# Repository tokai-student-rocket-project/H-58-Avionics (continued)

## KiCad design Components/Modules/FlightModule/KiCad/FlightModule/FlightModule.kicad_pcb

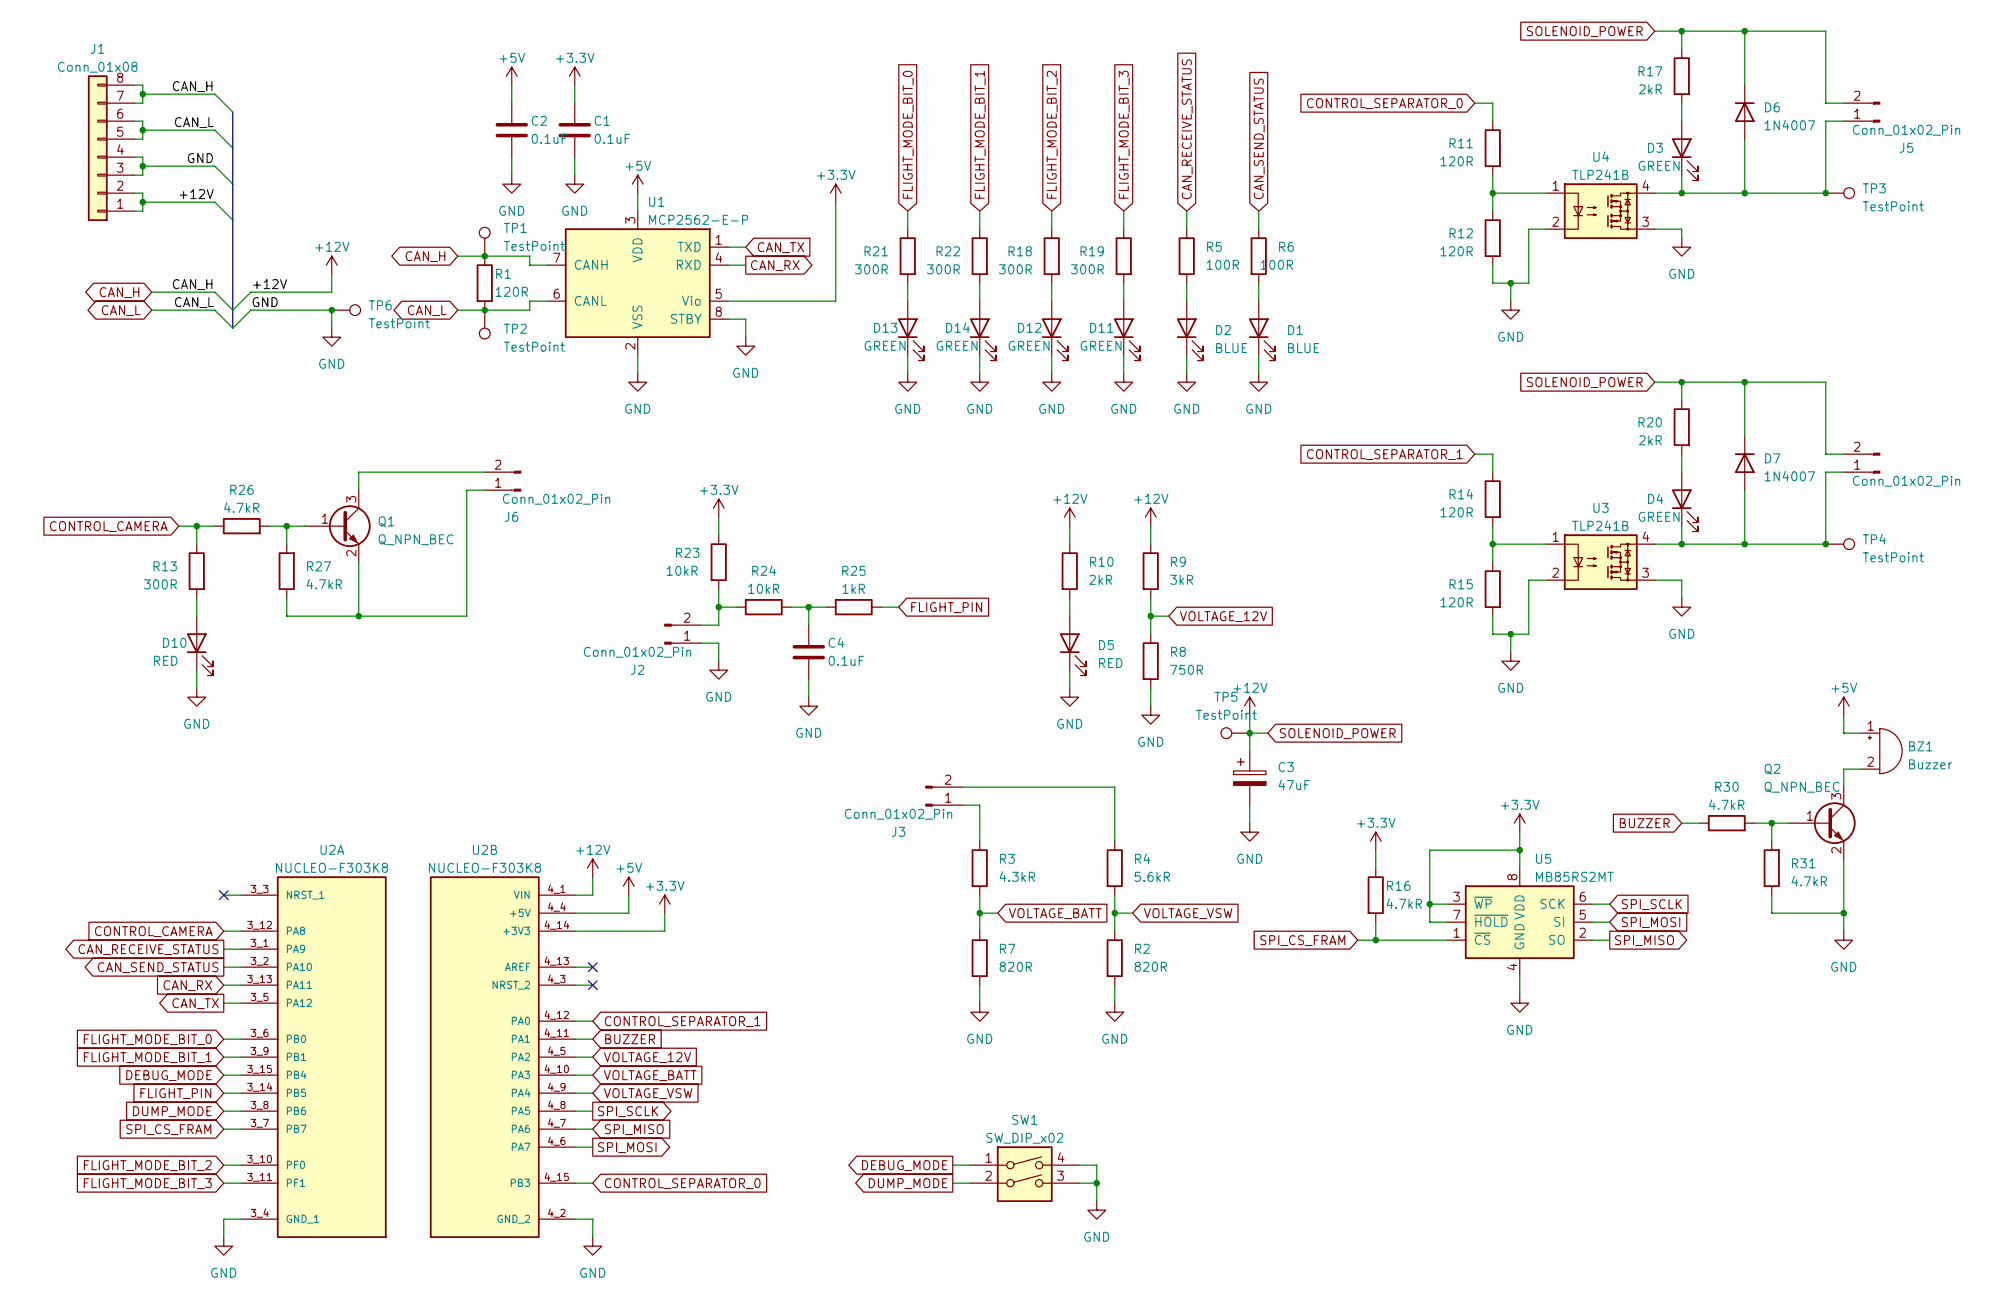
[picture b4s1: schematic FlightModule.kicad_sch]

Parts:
BZ1: Buzzer; Buzzer_12x9.5RM7.6
C1, C2, C4: 0.1uF; C_0603_1608Metric_Pad1.08x0.95mm_HandSolder
C3: 47uF; CP_Elec_6.3x5.9
D1, D2: BLUE; LED_0603_1608Metric_Pad1.05x0.95mm_HandSolder
D3, D4, D11, D12, D13, D14: GREEN; LED_0603_1608Metric_Pad1.05x0.95mm_HandSolder
D5, D10: RED; LED_0603_1608Metric_Pad1.05x0.95mm_HandSolder
D6, D7: 1N4007; D_SOD-123F
J1: Conn_01x08; Hirose_DF11B-8DP-2DS
J2, J3, J4, J5, J6: Conn_01x02_Pin; Hirose_DF1B
Q1, Q2: Q_NPN_BEC; SC-59_Handsoldering
R1, R11, R12, R14, R15: 120R; R_0603_1608Metric_Pad0.98x0.95mm_HandSolder
R2, R7: 820R; R_0603_1608Metric_Pad0.98x0.95mm_HandSolder
R3: 4.3kR; R_0603_1608Metric_Pad0.98x0.95mm_HandSolder
R4: 5.6kR; R_0603_1608Metric_Pad0.98x0.95mm_HandSolder
R5, R6: 100R; R_0805_2012Metric_Pad1.20x1.40mm_HandSolder
R8: 750R; R_0603_1608Metric_Pad0.98x0.95mm_HandSolder
R9: 3kR; R_0603_1608Metric_Pad0.98x0.95mm_HandSolder
R10, R17, R20: 2kR; R_0603_1608Metric_Pad0.98x0.95mm_HandSolder
R13, R18, R19, R21, R22: 300R; R_0603_1608Metric_Pad0.98x0.95mm_HandSolder
R16, R26, R27, R30, R31: 4.7kR; R_0603_1608Metric_Pad0.98x0.95mm_HandSolder
R23, R24: 10kR; R_0805_2012Metric_Pad1.20x1.40mm_HandSolder
R25: 1kR; R_0603_1608Metric_Pad0.98x0.95mm_HandSolder
SW1: SW_DIP_x02; SW_DIP_SPSTx02_Piano_10.8x6.64mm_W7.62mm_P2.54mm
TP1, TP2, TP3, TP4, TP5, TP6: TestPoint; Pin_D1.0mm_L10.0mm
U1: MCP2562-E-P; DIP-8_W7.62mm
U2: NUCLEO-F303K8; MODULE_NUCLEO-F303K8; PARTREV 5
U3, U4: TLP241B; DIP-4_W7.62mm
U5: MB85RS2MT; DIP-8_W7.62mm

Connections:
+3.3V: C1.1, R16.1, R23.1, U1.5 (Vio), U2.4_14 (+3V3), U5.3 (~WP), U5.7 (~HOLD), U5.8 (VDD)
+5V: BZ1.1 (-), C2.1, U1.3 (VDD), U2.4_4 (+5V)
BUZZER: R30.1, U2.4_11 (PA1)
CAN_H: J1.7, J1.8, R1.1, TP1.1, U1.7 (CANH)
CAN_L: J1.5, J1.6, R1.2, TP2.1, U1.6 (CANL)
CAN_RECEIVE_STATUS: R5.1, U2.3_1 (PA9)
CAN_RX: U1.4 (RXD), U2.3_13 (PA11)
CAN_SEND_STATUS: R6.1, U2.3_2 (PA10)
CAN_TX: U1.1 (TXD), U2.3_5 (PA12)
CONTROL_CAMERA: R13.1, R26.1, U2.3_12 (PA8)
CONTROL_SEPARATOR_0: R11.1, U2.4_15 (PB3)
CONTROL_SEPARATOR_1: R14.1, U2.4_12 (PA0)
DEBUG_MODE: SW1.1, U2.3_15 (PB4)
DUMP_MODE: SW1.2, U2.3_8 (PB6)
FLIGHT_MODE_BIT_0: R21.1, U2.3_6 (PB0)
FLIGHT_MODE_BIT_1: R22.1, U2.3_9 (PB1)
FLIGHT_MODE_BIT_2: R18.1, U2.3_10 (PF0)
FLIGHT_MODE_BIT_3: R19.1, U2.3_11 (PF1)
FLIGHT_PIN: R25.1, U2.3_14 (PB5)
GND: C1.2, C2.2, C3.2, C4.2, D1.1 (K), D2.1 (K), D5.1 (K), D10.1 (K), D11.1 (K), D12.1 (K), D13.1 (K), D14.1 (K), J1.3, J1.4, J2.1, Q2.2 (E), R2.2, R7.2, R8.2, R12.2, R15.2, R31.1, SW1.3, SW1.4, TP6.1, U1.2 (VSS), U1.8 (STBY), U2.3_4 (GND_1), U2.4_2 (GND_2), U3.2, U3.3, U4.2, U4.3, U5.4 (GND)
unnamed: BZ1.2 (+), Q2.3 (C)
unnamed: C4.1, R24.1, R25.2
unnamed: D1.2 (A), R6.2
unnamed: D2.2 (A), R5.2
unnamed: D3.2 (A), R17.2
unnamed: D3.1 (K), D6.2 (A), J5.1, TP3.1, U4.4
unnamed: D4.2 (A), R20.2
unnamed: D4.1 (K), D7.2 (A), J4.1, TP4.1, U3.4
unnamed: D5.2 (A), R10.2
unnamed: D10.2 (A), R13.2
unnamed: D11.2 (A), R19.2
unnamed: D12.2 (A), R18.2
unnamed: D13.2 (A), R21.2
unnamed: D14.2 (A), R22.2
unnamed: J2.2, R23.2, R24.2
unnamed: J3.1, R3.1
unnamed: J3.2, R4.1
unnamed: J6.1, Q1.2 (E), R27.1
unnamed: J6.2, Q1.3 (C)
unnamed: Q1.1 (B), R26.2, R27.2
unnamed: Q2.1 (B), R30.2, R31.2
unnamed: R11.2, R12.1, U4.1
unnamed: R14.2, R15.1, U3.1
SOLENOID_POWER: C3.1, D6.1 (K), D7.1 (K), J1.1, J1.2, J4.2, J5.2, R9.1, R10.1, R17.1, R20.1, TP5.1, U2.4_1 (VIN)
SPI_CS_FRAM: R16.2, U2.3_7 (PB7), U5.1 (~CS)
SPI_MISO: U2.4_7 (PA6), U5.2 (SO)
SPI_MOSI: U2.4_6 (PA7), U5.5 (SI)
SPI_SCLK: U2.4_8 (PA5), U5.6 (SCK)
VOLTAGE_12V: R8.1, R9.2, U2.4_5 (PA2)
VOLTAGE_BATT: R3.2, R7.1, U2.4_10 (PA3)
VOLTAGE_VSW: R2.1, R4.2, U2.4_9 (PA4)

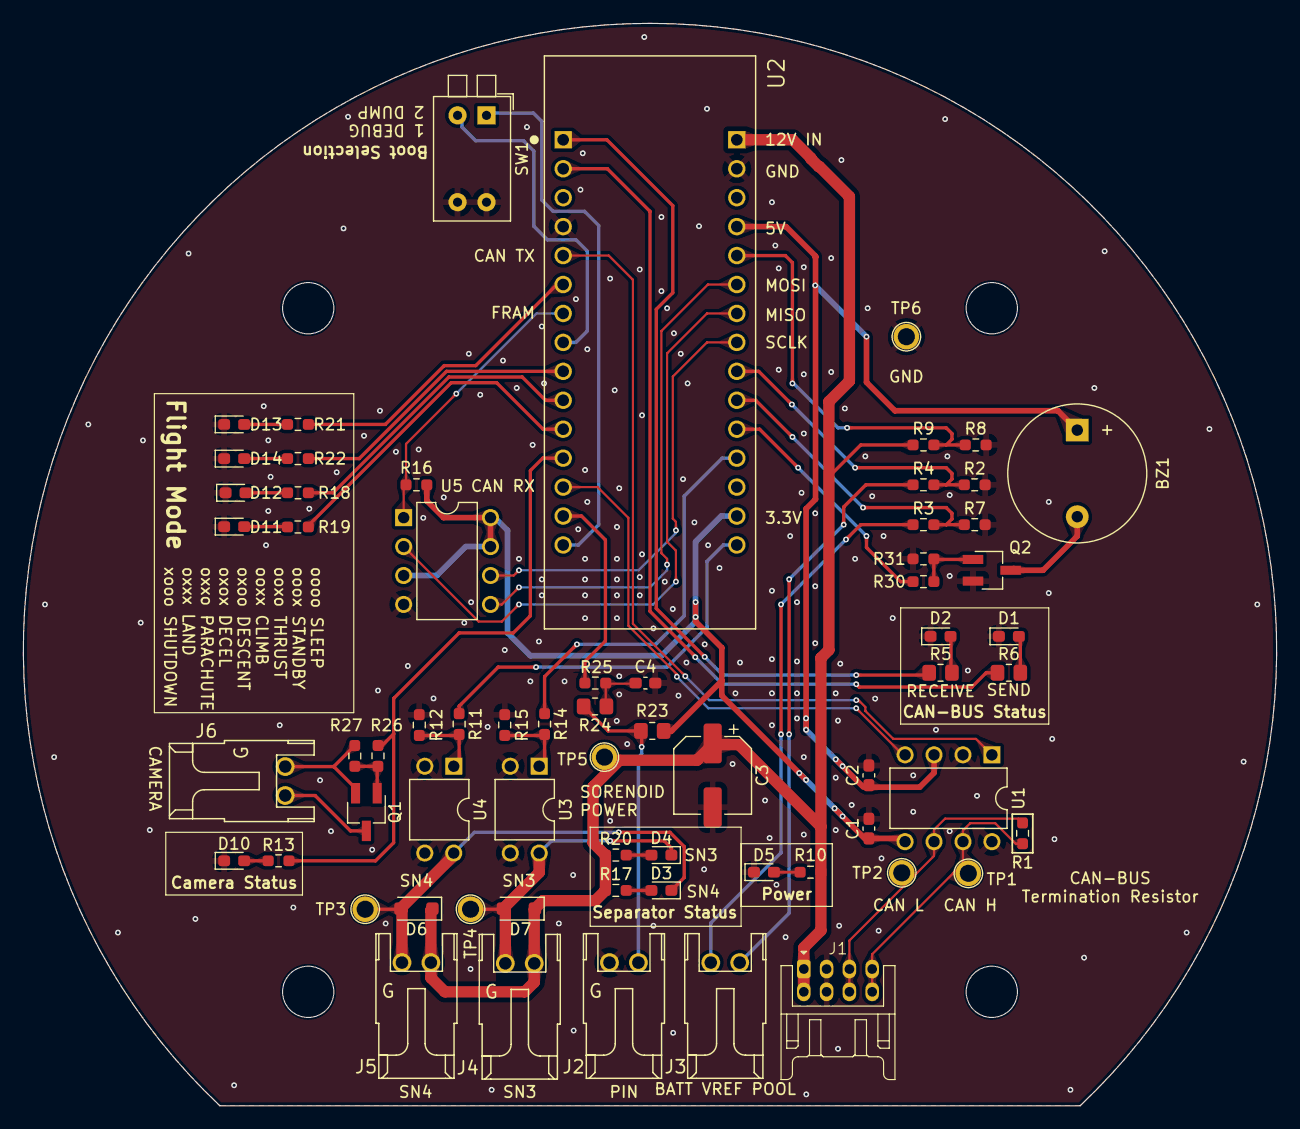
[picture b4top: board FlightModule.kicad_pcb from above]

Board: 2 copper layers, 110.0 x 95.0 mm, 67 parts (0 on the bottom side), 51 nets.

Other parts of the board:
e: MountingHole_4.5mm

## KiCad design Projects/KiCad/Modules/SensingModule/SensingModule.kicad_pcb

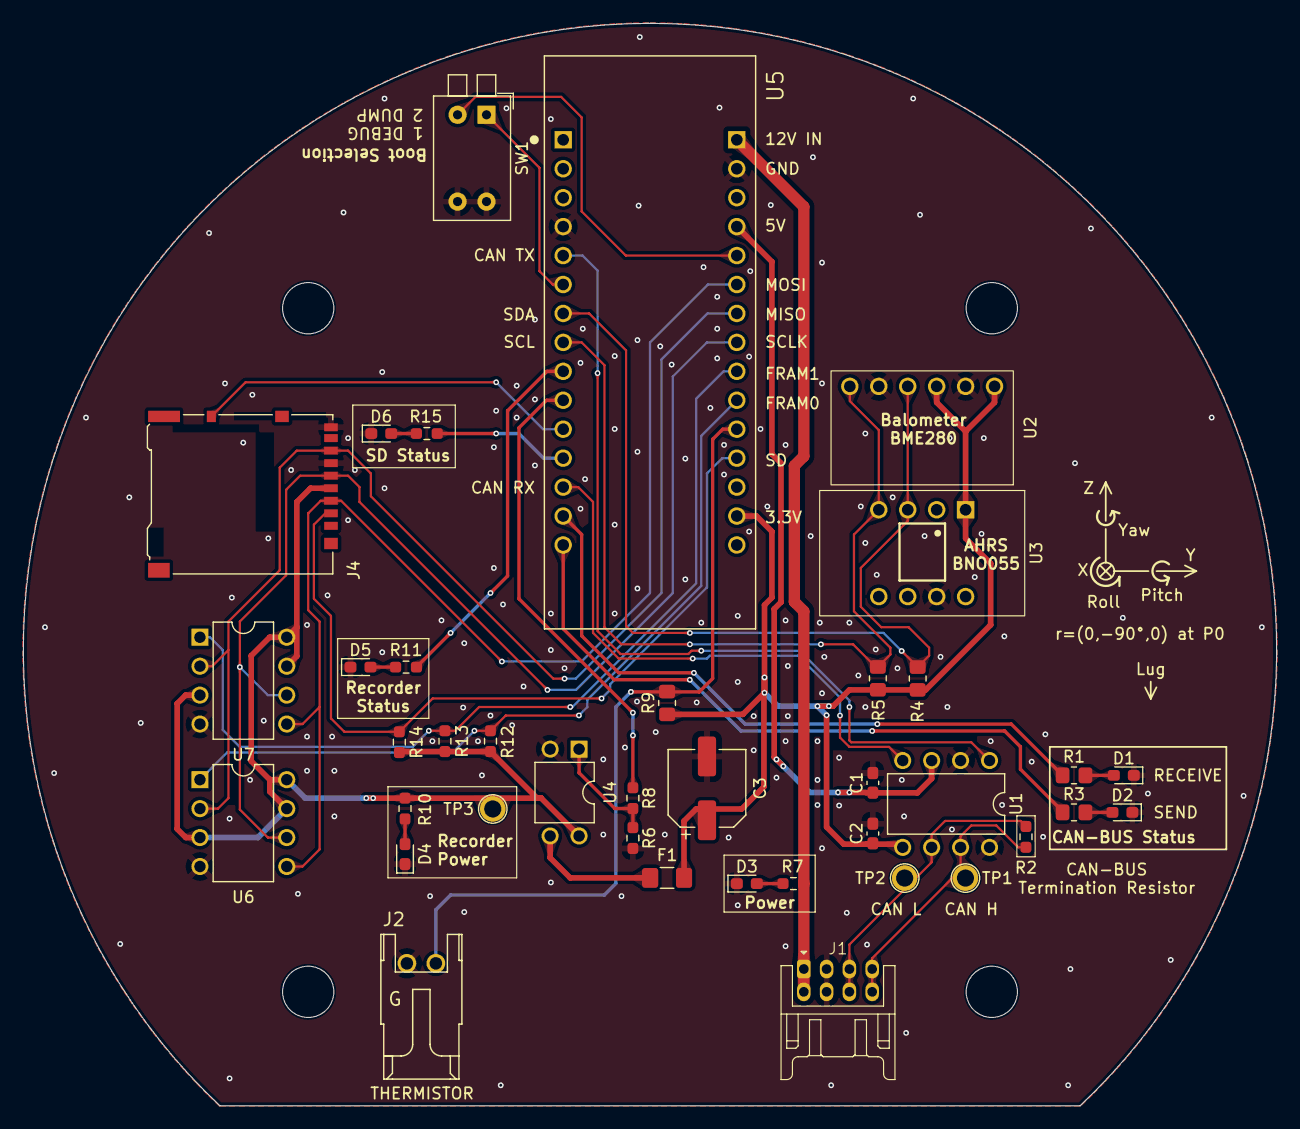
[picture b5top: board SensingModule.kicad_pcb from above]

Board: 2 copper layers, 110.0 x 95.0 mm, 39 parts (0 on the bottom side), 34 nets.

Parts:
C1, C2: 0.1uF; C_0603_1608Metric_Pad1.08x0.95mm_HandSolder
C3: 47uF; CP_Elec_6.3x5.9
D1, D2: BLUE; LED_0603_1608Metric_Pad1.05x0.95mm_HandSolder
D3, D4: RED; LED_0603_1608Metric_Pad1.05x0.95mm_HandSolder
D5, D6: GREEN; LED_0603_1608Metric_Pad1.05x0.95mm_HandSolder
F1: Polyfuse; Fuse_1206_3216Metric_Pad1.42x1.75mm_HandSolder
J1: Conn_01x08; Hirose_DF11B-8DP-2DS
J2: Conn_01x02_Pin; Hirose_DF1B
J4: Micro_SD_Card_Det_Hirose_DM3AT; microSD_HC_Hirose_DM3AT-SF-PEJM5
R1, R3: 100R; R_0805_2012Metric_Pad1.20x1.40mm_HandSolder
R2, R6, R8: 120R; R_0603_1608Metric_Pad0.98x0.95mm_HandSolder
R4, R5, R9: 10kR; R_0805_2012Metric_Pad1.20x1.40mm_HandSolder
R7: 2kR; R_0603_1608Metric_Pad0.98x0.95mm_HandSolder
R10, R11, R15: 300R; R_0603_1608Metric_Pad0.98x0.95mm_HandSolder
R12, R13, R14: 4.7kR; R_0603_1608Metric_Pad0.98x0.95mm_HandSolder
SW1: SW_DIP_x02; SW_DIP_SPSTx02_Piano_10.8x6.64mm_W7.62mm_P2.54mm
TP1, TP2, TP3: TestPoint; Pin_D1.0mm_L10.0mm
U1: MCP2562-E-P; DIP-8_W7.62mm
U2: BME280
U3: BNO055
U4: TLP241B; DIP-4_W7.62mm
U5: NUCLEO-F303K8; MODULE_NUCLEO-F303K8
U6, U7: MB85RS2MT; DIP-8_W7.62mm

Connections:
+3.3V: C2.1, C3.1, F1.1, R4.1, R5.1, R9.1, U1.5 (Vio), U2.1 (VDD), U2.3 (SCB), U3.1 (VIN), U5.4_14 (+3V3)
+5V: C1.1, U1.3 (VDD), U5.4_4 (+5V)
+12V: J1.1, J1.2, R7.1, U5.4_1 (VIN)
CAN_H: J1.7, J1.8, R2.1, TP1.1, U1.7 (CANH)
CAN_L: J1.5, J1.6, R2.2, TP2.1, U1.6 (CANL)
CAN_RECEIVE_STATUS: R1.1, U5.3_14 (PB5)
CAN_RX: U1.4 (RXD), U5.3_13 (PA11)
CAN_SEND_STATUS: R3.1, U5.3_15 (PB4)
CAN_TX: U1.1 (TXD), U5.3_5 (PA12)
DEBUG_MODE: SW1.1, U5.3_6 (PB0)
DUMP_MODE: SW1.2, U5.4_5 (PA2)
GND: C1.2, C2.2, C3.2, D1.1 (K), D2.1 (K), D3.1 (K), D4.1 (K), D5.1 (K), D6.1 (K), J1.3, J1.4, J2.1, J4.6 (VSS), J4.9 (DET_B), R6.2, SW1.3, SW1.4, U1.2 (VSS), U1.8 (STBY), U2.2 (GND), U2.5 (SDO), U3.7 (GND), U4.2, U5.3_4 (GND_1), U5.4_2 (GND_2), U6.4 (GND), U7.4 (GND)
I2C_SCL: R5.2, U2.6 (SCK), U3.4 (SCL/R), U5.3_8 (PB6)
I2C_SDA: R4.2, U2.4 (SDI), U3.3 (SDA/T), U5.3_7 (PB7)
unnamed: D1.2 (A), R1.2
unnamed: D2.2 (A), R3.2
unnamed: D3.2 (A), R7.2
unnamed: D4.2 (A), R10.2
unnamed: D5.2 (A), R11.2
unnamed: D6.2 (A), R15.2
unnamed: F1.2, U4.3
unnamed: R6.1, R8.2, U4.1
RECORDER_POWER: J4.4 (VDD), R10.1, R12.1, R13.1, R14.1, TP3.1, U4.4, U6.3 (~WP), U6.7 (~HOLD), U6.8 (VDD), U7.3 (~WP), U7.7 (~HOLD), U7.8 (VDD)
RECORDER_POWER_CONTROL: R8.1, U5.3_10 (PF0)
RECORD_STATUS: R11.1, U5.3_9 (PB1)
SD_CHECK: J4.10 (DET_A), U5.3_11 (PF1)
SD_STATUS: R15.1, U5.3_12 (PA8)
SPI_CS_FRAM0: R12.2, U5.4_10 (PA3), U6.1 (~CS)
SPI_CS_FRAM1: R13.2, U5.4_9 (PA4), U7.1 (~CS)
SPI_CS_SD: J4.2 (DAT3/CD), R14.2, U5.4_12 (PA0)
SPI_MISO: J4.7 (DAT0), U5.4_7 (PA6), U6.2 (SO), U7.2 (SO)
SPI_MOSI: J4.3 (CMD), U5.4_6 (PA7), U6.5 (SI), U7.5 (SI)
SPI_SCLK: J4.5 (CLK), U5.4_8 (PA5), U6.6 (SCK), U7.6 (SCK)
THERMISTOR: J2.2, R9.2, U5.4_11 (PA1)

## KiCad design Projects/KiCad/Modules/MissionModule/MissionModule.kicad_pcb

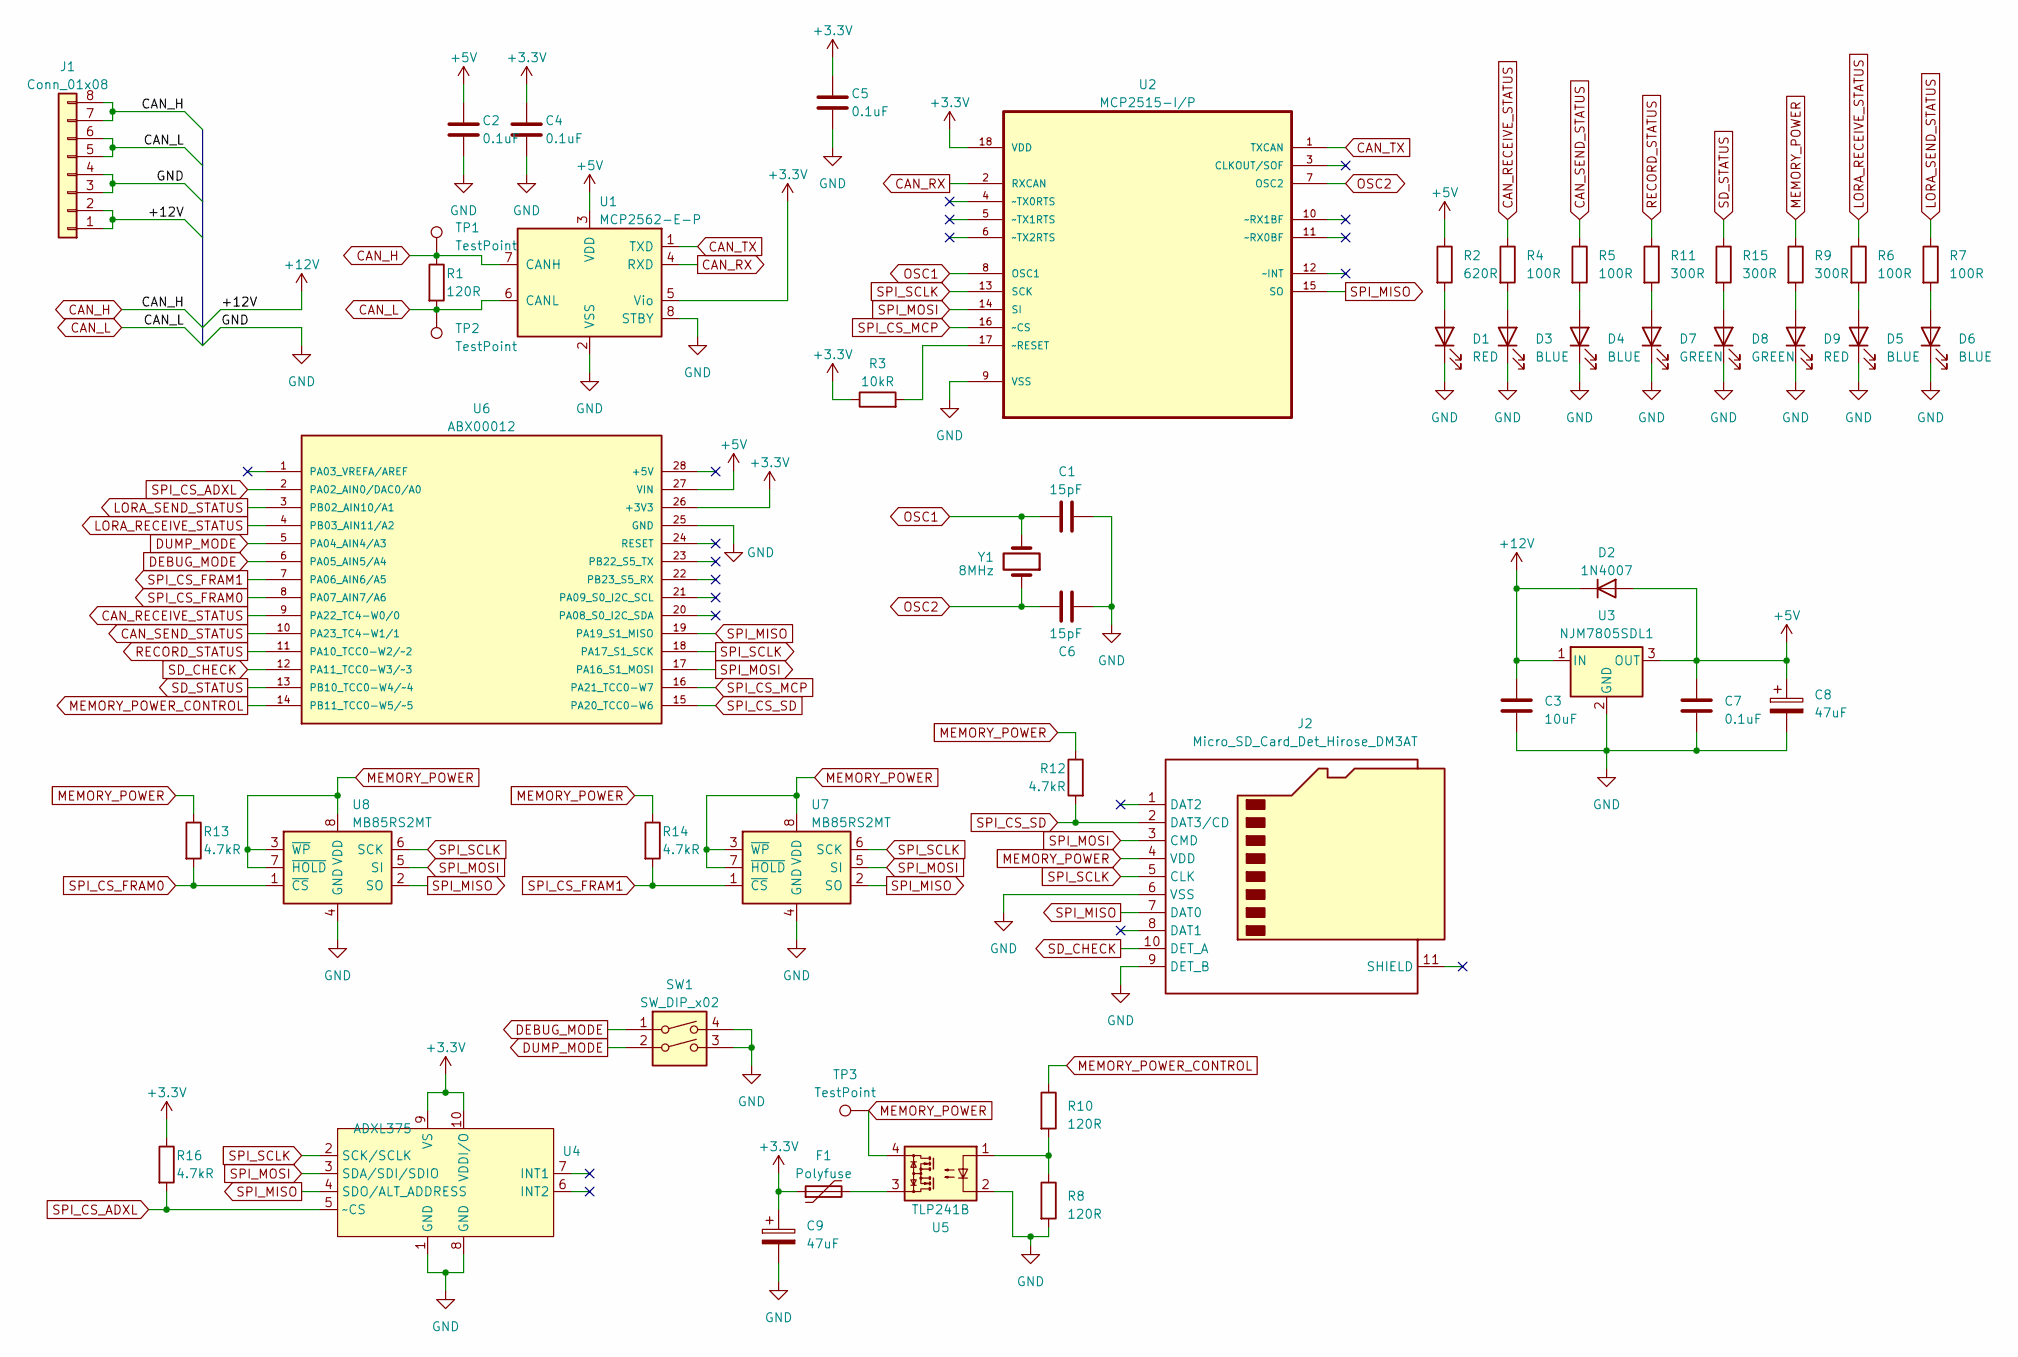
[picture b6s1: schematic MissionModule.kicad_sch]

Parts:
C1, C6: 15pF; C_0603_1608Metric_Pad1.08x0.95mm_HandSolder
C2, C4, C5, C7: 0.1uF; C_0603_1608Metric_Pad1.08x0.95mm_HandSolder
C3: 10uF; C_0603_1608Metric_Pad1.08x0.95mm_HandSolder
C8, C9: 47uF; CP_Elec_6.3x5.9
D1, D9: RED; LED_0603_1608Metric_Pad1.05x0.95mm_HandSolder
D2: 1N4007; D_SOD-123F
D3, D4, D5, D6: BLUE; LED_0603_1608Metric_Pad1.05x0.95mm_HandSolder
D7, D8: GREEN; LED_0603_1608Metric_Pad1.05x0.95mm_HandSolder
F1: Polyfuse; Fuse_1206_3216Metric_Pad1.42x1.75mm_HandSolder
J1: Conn_01x08; Hirose_DF11B-8DP-2DS
J2: Micro_SD_Card_Det_Hirose_DM3AT; microSD_HC_Hirose_DM3AT-SF-PEJM5
R1, R8, R10: 120R; R_0603_1608Metric_Pad0.98x0.95mm_HandSolder
R2: 620R; R_0603_1608Metric_Pad0.98x0.95mm_HandSolder
R3: 10kR; R_0805_2012Metric_Pad1.20x1.40mm_HandSolder
R4, R5, R6, R7: 100R; R_0805_2012Metric_Pad1.20x1.40mm_HandSolder
R9, R11, R15: 300R; R_0603_1608Metric_Pad0.98x0.95mm_HandSolder
R12, R13, R14, R16: 4.7kR; R_0603_1608Metric_Pad0.98x0.95mm_HandSolder
SW1: SW_DIP_x02; SW_DIP_SPSTx02_Piano_10.8x6.64mm_W7.62mm_P2.54mm
TP1, TP2, TP3: TestPoint; Pin_D1.0mm_L10.0mm
U1: MCP2562-E-P; DIP-8_W7.62mm
U2: MCP2515-I/P; DIP-18_W7.62mm; MPN MCP2515-I/P
U3: NJM7805SDL1; TO-252-2
U4: ADXL375
U5: TLP241B; DIP-4_W7.62mm
U6: ABX00012; ARDUINO_ABX00012; PARTREV 5
U7, U8: MB85RS2MT; DIP-8_W7.62mm
Y1: 8MHz; Crystal_SMD_HC49-SD

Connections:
+3.3V: C4.1, C5.1, C9.1, F1.1, R3.1, R16.1, U1.5 (Vio), U2.18 (VDD), U4.9 (VS), U4.10 (VDDI/O), U6.26 (+3V3)
+5V: C2.1, C7.1, C8.1, D2.2 (A), R2.1, U1.3 (VDD), U3.3 (OUT), U6.27 (VIN)
+12V: C3.1, D2.1 (K), J1.1, J1.2, U3.1 (IN)
CAN_H: J1.7, J1.8, R1.1, TP1.1, U1.7 (CANH)
CAN_L: J1.5, J1.6, R1.2, TP2.1, U1.6 (CANL)
CAN_RECEIVE_STATUS: R4.1, U6.9 (PA22_TC4-W0/0)
CAN_RX: U1.4 (RXD), U2.2 (RXCAN)
CAN_SEND_STATUS: R5.1, U6.10 (PA23_TC4-W1/1)
CAN_TX: U1.1 (TXD), U2.1 (TXCAN)
DEBUG_MODE: SW1.1, U6.6 (PA05_AIN5/A4)
DUMP_MODE: SW1.2, U6.5 (PA04_AIN4/A3)
GND: C1.1, C2.2, C3.2, C4.2, C5.2, C6.1, C7.2, C8.2, C9.2, D1.1 (K), D3.1 (K), D4.1 (K), D5.1 (K), D6.1 (K), D7.1 (K), D8.1 (K), D9.1 (K), J1.3, J1.4, J2.6 (VSS), J2.9 (DET_B), R8.2, SW1.3, SW1.4, U1.2 (VSS), U1.8 (STBY), U2.9 (VSS), U3.2 (GND), U4.1 (GND), U4.8 (GND), U5.2, U6.25 (GND), U7.4 (GND), U8.4 (GND)
LORA_RECEIVE_STATUS: R6.1, U6.4 (PB03_AIN11/A2)
LORA_SEND_STATUS: R7.1, U6.3 (PB02_AIN10/A1)
MEMORY_POWER: J2.4 (VDD), R9.1, R12.1, R13.1, R14.1, TP3.1, U5.4, U7.3 (~WP), U7.7 (~HOLD), U7.8 (VDD), U8.3 (~WP), U8.7 (~HOLD), U8.8 (VDD)
MEMORY_POWER_CONTROL: R10.1, U6.14 (PB11_TCC0-W5/~5)
unnamed: D1.2 (A), R2.2
unnamed: D3.2 (A), R4.2
unnamed: D4.2 (A), R5.2
unnamed: D5.2 (A), R6.2
unnamed: D6.2 (A), R7.2
unnamed: D7.2 (A), R11.2
unnamed: D8.2 (A), R15.2
unnamed: D9.2 (A), R9.2
unnamed: F1.2, U5.3
unnamed: R8.1, R10.2, U5.1
unnamed: R3.2, U2.17 (~RESET)
OSC1: C1.2, U2.8 (OSC1), Y1.2
OSC2: C6.2, U2.7 (OSC2), Y1.1
RECORD_STATUS: R11.1, U6.11 (PA10_TCC0-W2/~2)
SD_CHECK: J2.10 (DET_A), U6.12 (PA11_TCC0-W3/~3)
SD_STATUS: R15.1, U6.13 (PB10_TCC0-W4/~4)
SPI_CS_ADXL: R16.2, U4.5 (~CS), U6.2 (PA02_AIN0/DAC0/A0)
SPI_CS_FRAM0: R13.2, U6.8 (PA07_AIN7/A6), U8.1 (~CS)
SPI_CS_FRAM1: R14.2, U6.7 (PA06_AIN6/A5), U7.1 (~CS)
SPI_CS_MCP: U2.16 (~CS), U6.16 (PA21_TCC0-W7)
SPI_CS_SD: J2.2 (DAT3/CD), R12.2, U6.15 (PA20_TCC0-W6)
SPI_MISO: J2.7 (DAT0), U2.15 (SO), U4.4 (SDO/ALT_ADDRESS), U6.19 (PA19_S1_MISO), U7.2 (SO), U8.2 (SO)
SPI_MOSI: J2.3 (CMD), U2.14 (SI), U4.3 (SDA/SDI/SDIO), U6.17 (PA16_S1_MOSI), U7.5 (SI), U8.5 (SI)
SPI_SCLK: J2.5 (CLK), U2.13 (SCK), U4.2 (SCK/SCLK), U6.18 (PA17_S1_SCK), U7.6 (SCK), U8.6 (SCK)

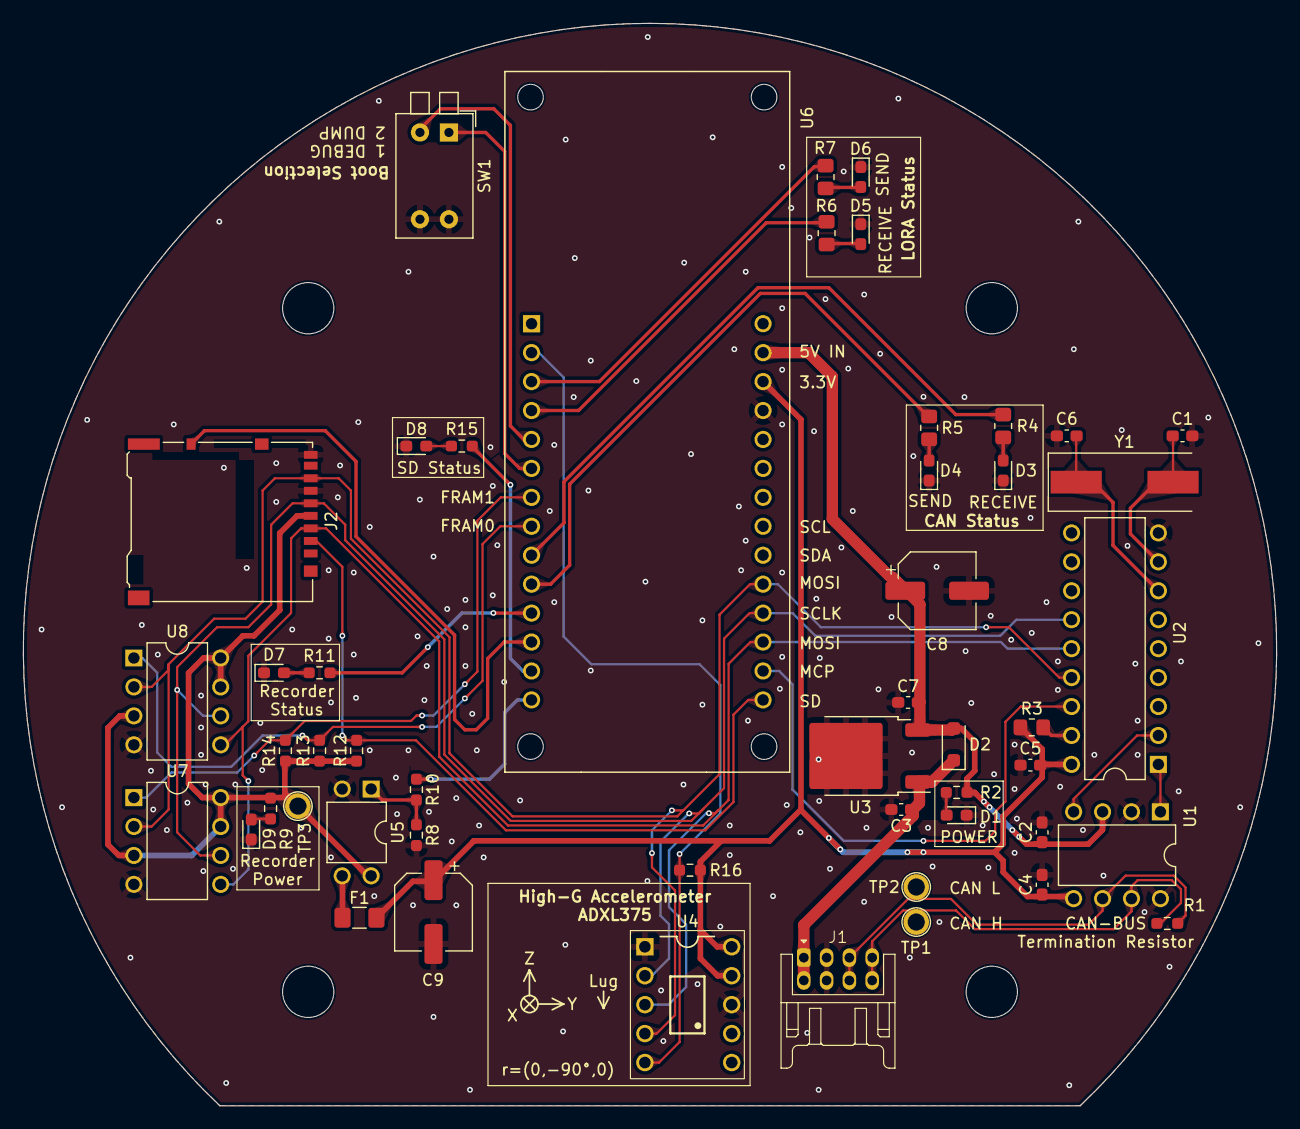
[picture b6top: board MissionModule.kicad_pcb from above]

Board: 2 copper layers, 110.0 x 95.0 mm, 50 parts (0 on the bottom side), 40 nets.

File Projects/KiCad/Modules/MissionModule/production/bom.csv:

Designator,Footprint,Quantity,Value,LCSC Part #
"C1, C6",0603,2,15pF,
"C2, C4, C5, C7",0603,4,0.1uF,
C3,0603,1,10uF,
"C8, C9",CP_Elec_6.3x5.9,2,47uF,
"D1, D9",0603,2,RED,
D2,D_SOD-123F,1,1N4007,
"D3, D4, D5, D6",0603,4,BLUE,
"D7, D8",0603,2,GREEN,
F1,1206,1,Polyfuse,
J1,Hirose_DF11B-8DP-2DS,1,Conn_01x08,
J2,microSD_HC_Hirose_DM3AT-SF-PEJM5,1,Micro_SD_Card_Det_Hirose_DM3AT,
"R1, R10, R8",0603,3,120R,
"R11, R15, R9",0603,3,300R,
"R12, R13, R14, R16",0603,4,4.7kR,
R2,0603,1,620R,
R3,0805,1,10kR,
"R4, R5, R6, R7",0805,4,100R,
SW1,SW_DIP_SPSTx02_Piano_10.8x6.64mm_W7.62mm_P2.54mm,1,SW_DIP_x02,
"TP1, TP2, TP3",Pin_D1.0mm_L10.0mm,3,TestPoint,
U1,DIP-8_W7.62mm,1,MCP2562-E-P,
U2,DIP-18_W7.62mm,1,MCP2515-I/P,MCP2515-I/P
U3,TO-252-2,1,NJM7805SDL1,
U4,ADXL375,1,ADXL375,
U5,DIP-4_W7.62mm,1,TLP241B,
U6,ARDUINO_ABX00012,1,ABX00012,
"U7, U8",DIP-8_W7.62mm,2,MB85RS2MT,
Y1,Crystal_SMD_HC49-SD,1,8MHz,

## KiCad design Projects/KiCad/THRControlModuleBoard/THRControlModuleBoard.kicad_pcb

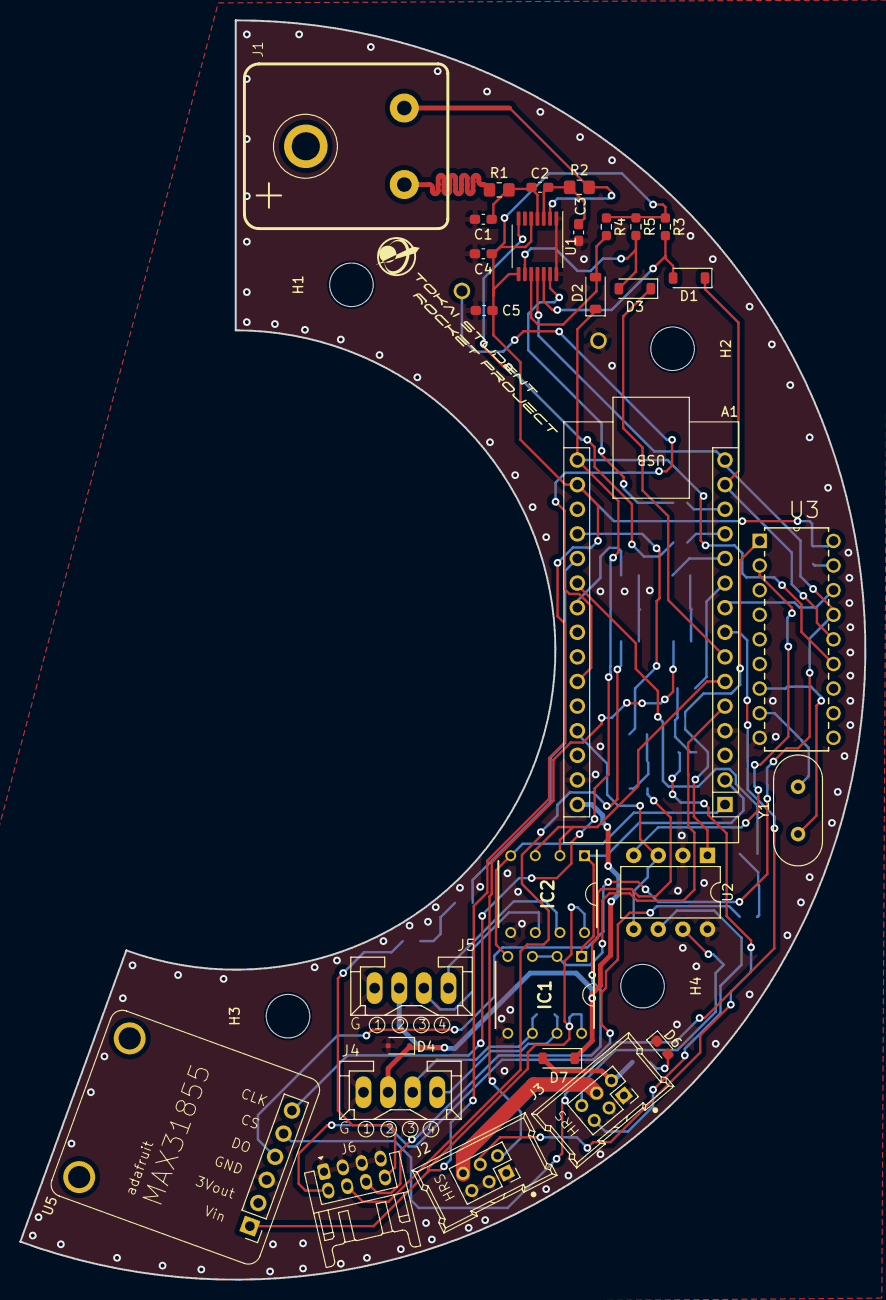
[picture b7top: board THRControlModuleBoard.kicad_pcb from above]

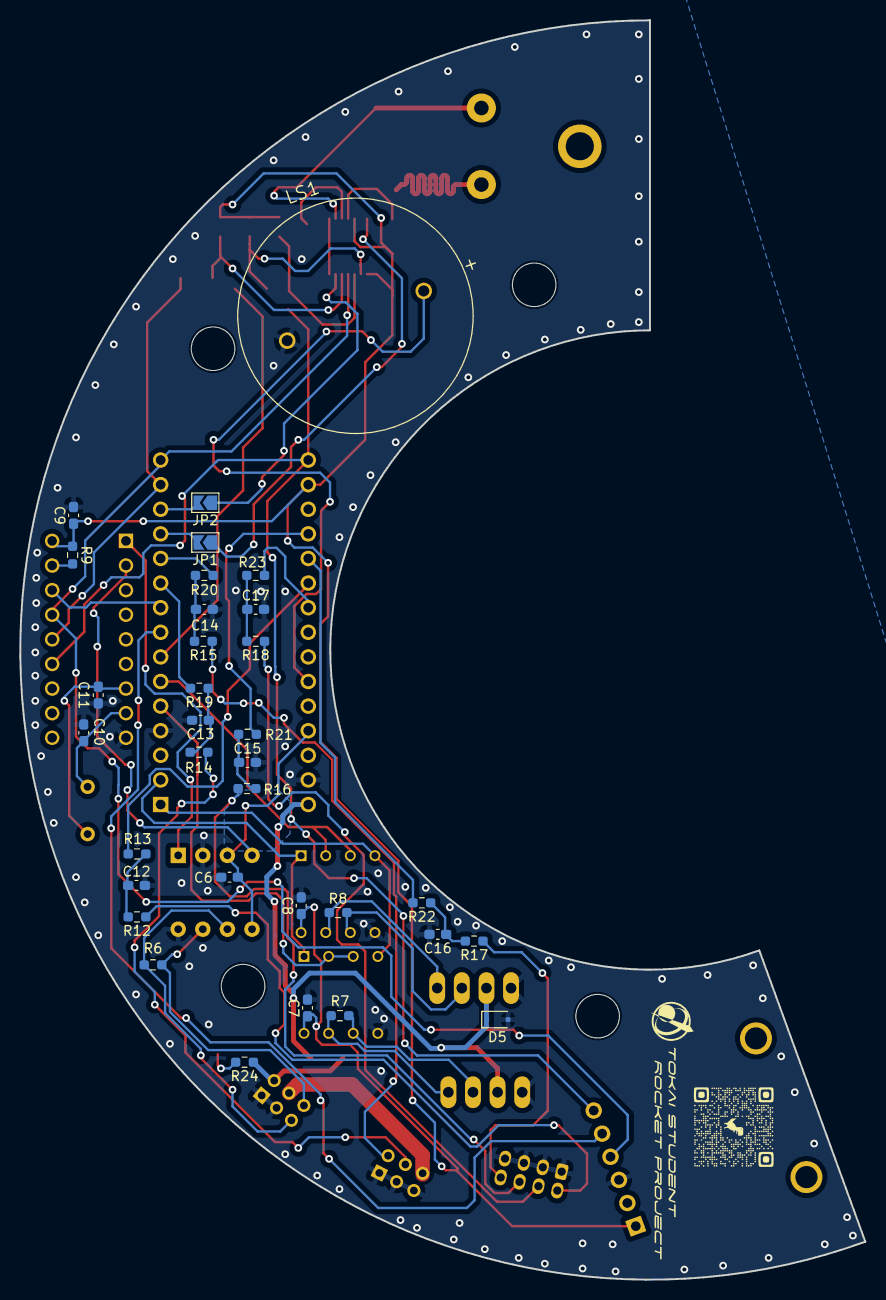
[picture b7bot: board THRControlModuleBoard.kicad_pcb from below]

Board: 2 copper layers, 87.2 x 130.0 mm, 67 parts (33 on the bottom side), 58 nets.

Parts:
A1: Arduino_Nano_Every; Arduino_Nano
C1, C3: 0.01uF; C_0603_1608Metric_Pad1.08x0.95mm_HandSolder
C2, C4, C5, C6, C7, C8, C9, C12, C13, C14, C15, C16, C17: 0.1uF; C_0603_1608Metric_Pad1.08x0.95mm_HandSolder
C10, C11: 15pF; C_0603_1608Metric_Pad1.08x0.95mm_HandSolder
D1, D2, D3: D; D_SOD-123
D4, D5: MM3Zxx; D_SOD-323F
D6: LED; LED_0603_1608Metric_Pad1.05x0.95mm_HandSolder
D7: 1N4148W; D_SOD-123
H1, H2, H3, H4: MountingHole; MountingHole_4.5mm
IC1, IC2: LTC1480CN8#PBF; DIP794W53P254L1016H394Q8N
J1: Screw_Terminal_01x02; RS_PRO_611-8157
J2, J3: Conn_02x03_Odd_Even; Hirose_DF51A-6DP-2DSA
J4, J5: Conn_01x04; CONNECTOR_4-STRAIGHT
J6: Conn_02x04_Odd_Even; Hirose_DF11B-8DP-2DS
JP1, JP2: SolderJumper_2_Bridged; SolderJumper-2_P1.3mm_Open_TrianglePad1.0x1.5mm
LS1: PKB24SPCH3601-B0; SPKR_PKB24SPCH3601-B0
R1, R2: 100; R_0805_2012Metric_Pad1.20x1.40mm_HandSolder
R3, R4, R5, R9, R12, R14, R15, R16, R17, R18: 10k; R_0603_1608Metric_Pad0.98x0.95mm_HandSolder
R6, R7, R8: 120; R_0603_1608Metric_Pad0.98x0.95mm_HandSolder
R13, R19, R20, R21, R22, R23, R24: 1k; R_0603_1608Metric_Pad0.98x0.95mm_HandSolder
U1: MAX31856MUD+T; TSSOP-14_4.4x5mm_P0.65mm
U2: Value: Value: Value: Value: MCP2562-E-P; DIP-8_W7.62mm
U3: MCP2515-I/P; DIP254P762X432-18
U5: MAX31855
Y1: 8MHz; Crystal_HC49-4H_Vertical

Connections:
+3.3V: A1.17 (3V3), C4.1, C5.1, C7.1, C8.1, C9.1, IC1.8 (VCC), IC2.8 (VCC), R3.1, R4.1, R5.1, R9.1, U1.5 (AVDD), U1.8 (DVDD), U3.18 (VDD), U5.1 (Vin)
+5V: A1.27 (+5V), C6.2, U2.3 (VDD), U2.5 (Vio)
+12V: A1.30 (VIN), D4.1 (K), D5.1 (K), D7.1 (K), J4.2, J5.2
+VDC: J2.6, J3.4
B3M_Servo__Close: A1.20 (A1), R22.2
B3M_Servo__Closeinput: J6.8, R17.1
B3M_Servo__Open: A1.19 (A0), R21.2
B3M_Servo__Openinput: J6.6, R16.1
BIAS: J1.1, R2.1, U1.2 (BIAS)
CAN__H: J3.6, R6.1, U2.7 (CANH)
CAN__L: J3.5, R6.2, U2.6 (CANL)
CAN__RXD-CANRX: U2.4 (RXD), U3.2 (RXCAN)
CAN__TXD-TXCAN: U2.1 (TXD), U3.1 (TXCAN)
DRDY: JP1.1 (A), U1.7 (~DRDY)
GND: A1.4 (GND), A1.29 (GND), C1.1, C3.2, C4.2, C5.2, C6.1, C7.2, C8.2, C9.2, C10.2, C11.2, C12.2, C13.2, C14.2, C15.2, C16.2, C17.2, D4.2 (A), D5.2 (A), D6.1 (K), IC1.5 (GND), IC2.5 (GND), J2.1, J2.3, J2.5, J3.1, J3.3, J4.1, J5.1, J6.1, J6.3, J6.5, J6.7, LS1.N, U1.1 (AGND), U1.14 (DGND), U2.2 (VSS), U2.8 (STBY), U3.9 (VSS), U5.3 (GND)
IO__Busser: A1.25 (A6), LS1.P
MAX31855__~CS-~CS: A1.8 (D5), U5.5 (~CS)
MAX31856__DRDY-DRDY: A1.12 (D9), JP1.2 (B)
MAX31856__FAULT-FAULT: A1.13 (D10), JP2.2 (B)
MAX31856__~CS-~CS: A1.7 (D4), D3.1 (K)
MCP2515__~CS-~CS: A1.9 (D6), U3.16 (~CS)
unnamed: C12.1, R12.2, R13.1
unnamed: C13.1, R14.2, R19.1
unnamed: C14.1, R15.2, R20.1
unnamed: C15.1, R16.2, R21.1
unnamed: C16.1, R17.2, R22.1
unnamed: C17.1, R18.2, R23.1
unnamed: D1.2 (A), R3.2, U1.12 (SDI)
unnamed: D2.2 (A), R4.2, U1.10 (SCK)
unnamed: D3.2 (A), R5.2, U1.9 (~CS)
unnamed: D6.2 (A), R24.2
unnamed: D7.2 (A), J3.2, R24.1
unnamed: J1.2, R1.1
unnamed: C1.2, C2.1, R1.2, U1.4 (T+)
unnamed: C2.2, C3.1, R2.2, U1.3 (T-)
unnamed: R9.2, U3.17 (~RESET)
OCS1: C10.1, U3.8 (OSC1), Y1.2
OCS2: C11.1, U3.7 (OSC2), Y1.1
RS405_Servo__Close: A1.22 (A3), R23.2
RS405_Servo__Closeinput: J6.4, R18.1
RS405_Servo__Open: A1.21 (A2), R13.2
RS405_Servo__Openinput: J6.2, R12.1
RS485__A1: IC1.6 (A), J4.3, R7.2
RS485__A2: IC2.6 (A), J5.3, R8.2
RS485__B1: IC1.7 (B), J4.4, R7.1
RS485__B2: IC2.7 (B), J5.4, R8.1
RS485__DI-TX: A1.1 (TX1), IC1.4 (DI), IC2.4 (DI)
RS485__ENABLE_B3M: A1.5 (D2), IC1.2 (~RE), IC1.3 (DE)
RS485__ENABLE_RS405: A1.6 (D3), IC2.2 (~RE), IC2.3 (DE)
RS485__RO-RX: A1.2 (RX1), IC1.1 (RO), IC2.1 (RO)
SPI__MISO: A1.15 (MISO), U1.11 (SDO), U3.15 (SO), U5.4 (DO)
SPI__MOSI: A1.14 (MOSI), D1.1 (K), U3.14 (SI)
SPI__SCLK: A1.16 (SCK), D2.1 (K), U3.13 (SCK), U5.6 (SCK)
Umbilical__launchInput: J2.4, R14.1
Umbilical__launchPin: A1.10 (D7), R19.2
Umbilical__waitingInput: J2.2, R15.1
Umbilical__waitingPin: A1.11 (D8), R20.2
~FAULT: JP2.1 (A), U1.13 (~FAULT)
